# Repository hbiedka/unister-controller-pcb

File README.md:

## Dude, I need professional-looking PCB with <n> dry-contact relays, <m> 230V on/off relays, <x> inputs and <y> opto-isolated inputs

After ~10 similar projects I used to make using perfboards and PCBs etched at home I have created this PCB project to utillize it in as many automation projects as possible.

|  |  |
|---|---|
| Front | Back |

# What does it have

* 2.54 mm perfboard-like field for whatever you want
* 4 relays
  * NO/NC dry contact
  * fused AC output with N and PE split into 2 circuits protected by separated fuses 
* 8x terminal outputs for general purpose (6 of them can be easily connected to GND
* 2x optoinolated input
  * dry contact
  * low-voltage wet contact
  * AC wet contact
* AC to low voltage converted (12V, 5V or similar) using HiLink HLK series
* optional LDO or DC/DC converter (the net is called 5V but it can be any voltage by using proper LDO or converter)
* power LED diode

# Some projects I have done based on this PCB

| | |
|---|---|
|  |  |

# Configuration and customisation options

## Relays

| Footprint | Dry contact output | Wet contact output (AC voltage out) |
|---|---|---|
| Kn_DRY (closer to relay) | Populate | Do not populate |
| Kn_230VAC (closer to edge) | Do not populate | Populate |
| KN_WET jumper | Do not populate | Populate using ~1mm^2 wire |

If you are using wet contact output(s), remember to populate F2 or F3 by fuse holder and provide a proper fuse. **Remember to select proper amperage based on fuse rate and wiring**

### Negative voltage controlled coils with common VCC voltage (recommended)
If you would like to use eg. NPN or MOSFET-N transistor to drive relay coils and supply it from Hi-Link supply voltage output:
* Short COM_RELAY with VCC - the best way is to use solder nieghbor points near D4
* Solder suppression diodes according to PCB symbol (bar is cathode)

### Negative voltage controlled coils with common LDO/converter output voltage
Like above, but short COM_RELAY to 5V net

### Positive voltage controlled coils with common ground
If you would like to use PNP or MOSFET-P transistors to drive relay coils:
* Short COM_RELAY with GND
* Solder suppression diodes **opposite to PCB symbol** (bar is anode)

## Optoisolated inputs

| Footprint | Dry contact (positive) | Dry contact (negative) | Wet contact (low voltage) | Wet contact (AC voltage) |
|---|---|---|---|---|
| J10/J11 | Solder 2-pole terminal to pins 1-2 (left), short pins 3-4 | Solder 2-pole terminal to pins 3-4 (right), short pins 1-2 | Solder 2-pole terminal to pins 2-3 (middle) | Solder 2-pole terminal to pins 2-3 (middle) |
| D6/D8 | Short | Short | Short | Populate |
| R3/R4 | Short | Short | Short | Populate |
| C4/C6 | Do not populate | Do not populate | Do not populate | Populate |
| D7/D9 | Do not populate | Do not populate | Do not populate | Populate |

For all cases:
* Populate R2/R5 - use proper resistance to provide suitable diode current with nominal voltage
* Use PC817 or similar transoptor

## Single DC voltage (no DC/DC or LDO)

Short pins 1 and 3 of U1

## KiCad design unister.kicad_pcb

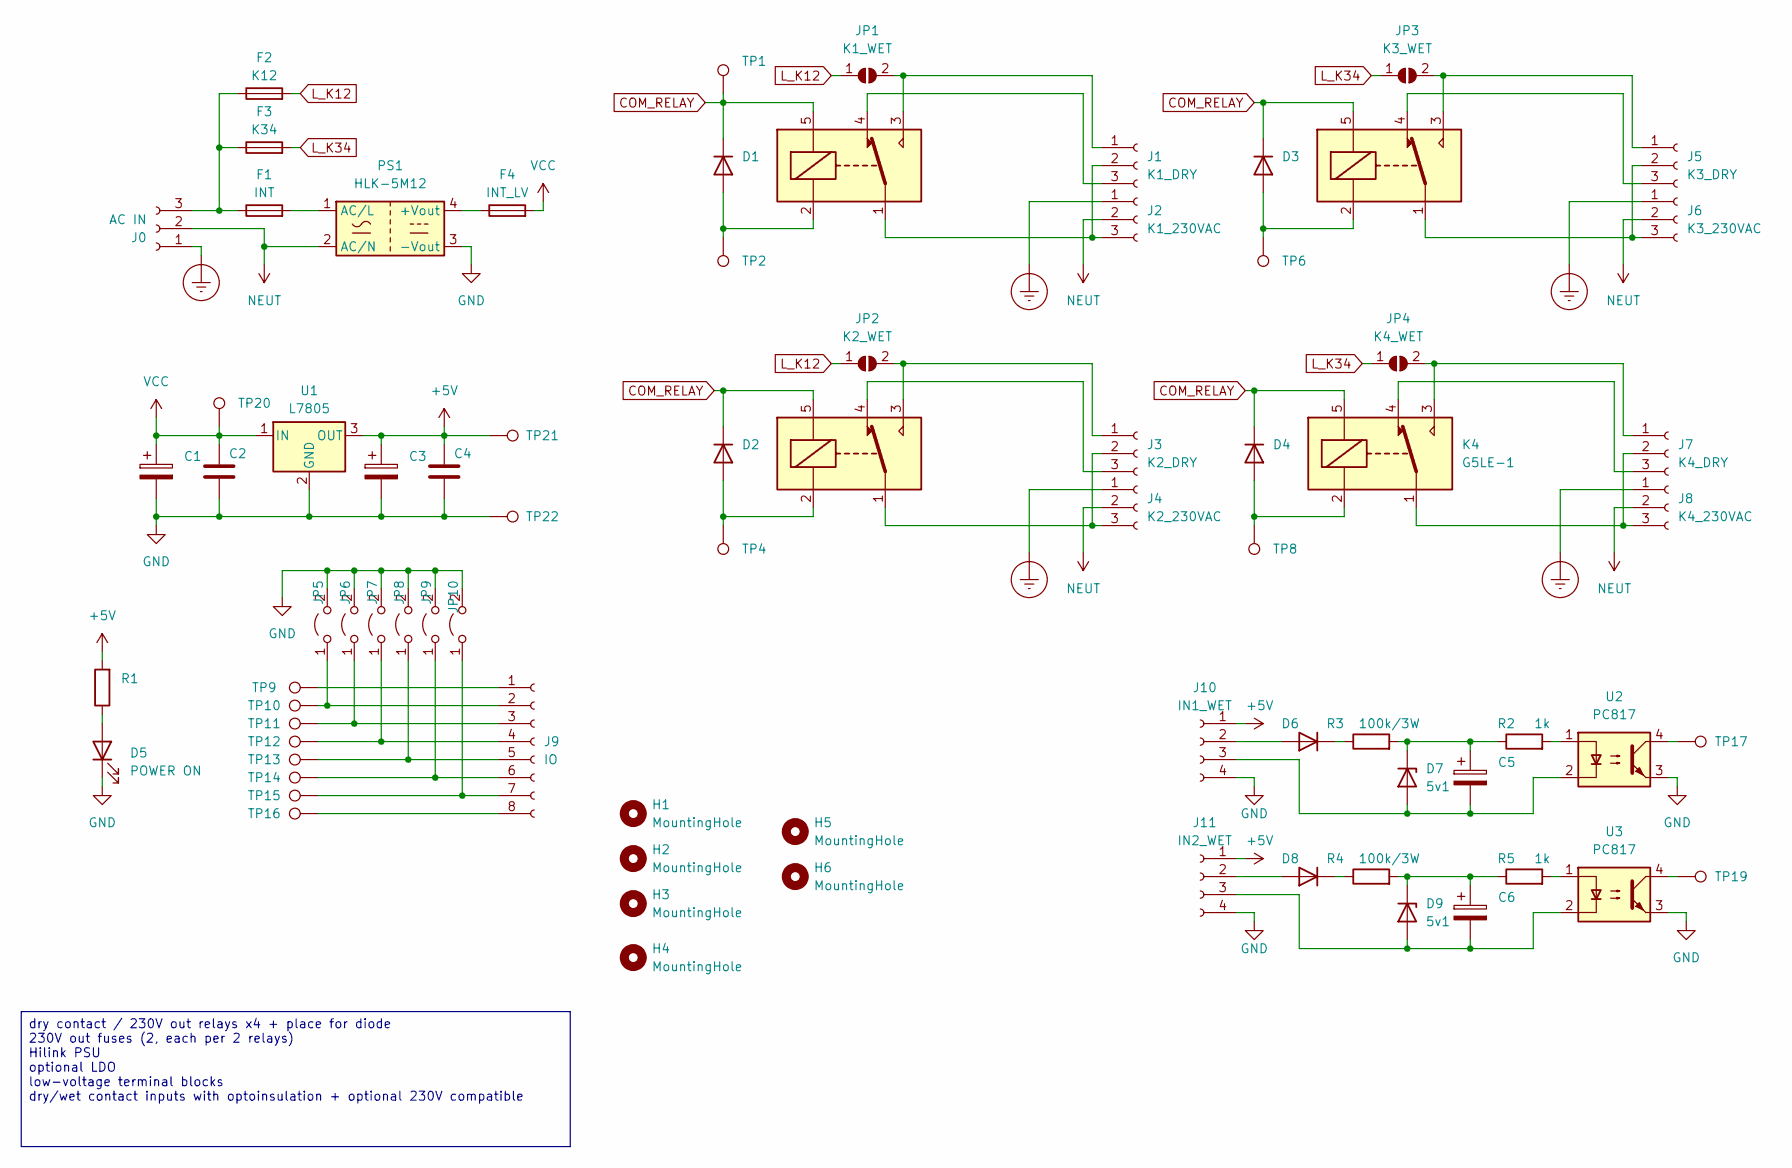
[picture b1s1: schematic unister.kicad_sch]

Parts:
C1, C3, C5, C6: C_Polarized; C_Radial_D10.0mm_H20.0mm_P5.00mm
C2, C4: C; C_Rect_L7.0mm_W3.5mm_P2.50mm_P5.00mm
D1, D2, D3, D4: 1N4007; D_DO-41_SOD81_P10.16mm_Horizontal
D5: POWER ON; LED_D3.0mm
D6, D8: D; D_DO-41_SOD81_P10.16mm_Horizontal
D7, D9: 5v1; D_DO-15_P5.08mm_Vertical_AnodeUp
F1: INT; Fuse_BelFuse_0ZRE0005FF_L8.3mm_W3.8mm
F2: K12; Fuseholder_Clip-5x20mm_Keystone_3512_Inline_P23.62x7.27mm_D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
F3: K34; Fuseholder_Clip-5x20mm_Keystone_3512_Inline_P23.62x7.27mm_D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
F4: INT_LV; Fuse_BelFuse_0ZRE0005FF_L8.3mm_W3.8mm
H1, H2, H3, H4, H5, H6: MountingHole; MountingHole_2.2mm_M2
J0: AC IN; PhoenixContact_MCV_1,5_3-G-5.08_1x03_P5.08mm_Vertical
J1: K1_DRY; PhoenixContact_MCV_1,5_3-G-5.08_1x03_P5.08mm_Vertical
J2: K1_230VAC; PhoenixContact_MCV_1,5_3-G-5.08_1x03_P5.08mm_Vertical
J3: K2_DRY; PhoenixContact_MCV_1,5_3-G-5.08_1x03_P5.08mm_Vertical
J4: K2_230VAC; PhoenixContact_MCV_1,5_3-G-5.08_1x03_P5.08mm_Vertical
J5: K3_DRY; PhoenixContact_MCV_1,5_3-G-5.08_1x03_P5.08mm_Vertical
J6: K3_230VAC; PhoenixContact_MCV_1,5_3-G-5.08_1x03_P5.08mm_Vertical
J7: K4_DRY; PhoenixContact_MCV_1,5_3-G-5.08_1x03_P5.08mm_Vertical
J8: K4_230VAC; PhoenixContact_MCV_1,5_3-G-5.08_1x03_P5.08mm_Vertical
J9: IO; PhoenixContact_MCV_1,5_8-G-5.08_1x08_P5.08mm_Vertical
J10: IN1_WET; PhoenixContact_MCV_1,5_4-G-5.08_1x04_P5.08mm_Vertical
J11: IN2_WET; PhoenixContact_MCV_1,5_4-G-5.08_1x04_P5.08mm_Vertical
JP1: K1_WET; TestPoint_2Pads_Pitch5.08mm_Drill1.3mm
JP2: K2_WET; TestPoint_2Pads_Pitch5.08mm_Drill1.3mm
JP3: K3_WET; TestPoint_2Pads_Pitch5.08mm_Drill1.3mm
JP4: K4_WET; TestPoint_2Pads_Pitch5.08mm_Drill1.3mm
JP5, JP6, JP7, JP8, JP9, JP10: SolderJumper-2_P1.3mm_Open_RoundedPad1.0x1.5mm
K1, K2, K3, K4: G5LE-1; Relay_SPDT_Omron-G5LE-1
PS1: HLK-5M12; Converter_ACDC_HiLink_HLK-5Mxx
R1: R; R_1206_3216Metric_Pad1.30x1.75mm_HandSolder
R2, R5: 1k; R_1206_3216Metric_Pad1.30x1.75mm_HandSolder
R3, R4: 100k/3W; R_Axial_DIN0309_L9.0mm_D3.2mm_P15.24mm_Horizontal
TP1, TP2, TP4, TP6, TP8, TP9, TP10, TP11, TP12, TP13, TP14, TP15, TP16, TP17, TP19, TP20, TP21, TP22: TestPoint; Pin_D0.7mm_L6.5mm_W1.8mm_FlatFork
U1: L7805; TO-92L_Inline_Wide
U2, U3: PC817; DIP-4_W7.62mm

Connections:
+5V: C3.1, C4.1, J10.1, J11.1, R1.2, TP21.1, U1.3 (OUT)
COM_RELAY: D1.1 (K), D2.1 (K), D3.1 (K), D4.1 (K), K1.5, K2.5, K3.5, K4.5, TP1.1
Earth_Protective: J0.1, J2.1, J4.1, J6.1, J8.1
GND: C1.2, C2.2, C3.2, C4.2, D5.1 (K), J10.4, J11.4, JP5.2 (B), JP6.2 (B), JP7.2 (B), JP8.2 (B), JP9.2 (B), JP10.2 (B), PS1.3 (-Vout), TP22.1, U1.2 (GND), U2.3, U3.3
L_K12: F2.2, JP1.1 (A), JP2.1 (A)
L_K34: F3.2, JP3.1 (A), JP4.1 (A)
NEUT: J0.2, J2.2, J4.2, J6.2, J8.2, PS1.2 (AC/N)
unnamed: D1.2 (A), K1.2, TP2.1
unnamed: D2.2 (A), K2.2, TP4.1
unnamed: D3.2 (A), K3.2, TP6.1
unnamed: D4.2 (A), K4.2, TP8.1
unnamed: D5.2 (A), R1.1
unnamed: D6.2 (A), J10.2
unnamed: D6.1 (K), R3.1
unnamed: C5.2, D7.2 (A), J10.3, U2.2
unnamed: C5.1, D7.1 (K), R2.1, R3.2
unnamed: D8.2 (A), J11.2
unnamed: D8.1 (K), R4.1
unnamed: C6.2, D9.2 (A), J11.3, U3.2
unnamed: C6.1, D9.1 (K), R4.2, R5.1
unnamed: F1.1, F2.1, F3.1, J0.3
unnamed: J1.1, JP1.2 (B), K1.3
unnamed: J1.2, J2.3, K1.1
unnamed: J1.3, K1.4
unnamed: J3.1, JP2.2 (B), K2.3
unnamed: J3.2, J4.3, K2.1
unnamed: J3.3, K2.4
unnamed: J5.1, JP3.2 (B), K3.3
unnamed: J5.2, J6.3, K3.1
unnamed: J5.3, K3.4
unnamed: J7.1, JP4.2 (B), K4.3
unnamed: J7.2, J8.3, K4.1
unnamed: J7.3, K4.4
unnamed: J9.1, TP9.1
unnamed: J9.2, JP5.1 (A), TP10.1
unnamed: J9.3, JP6.1 (A), TP11.1
unnamed: J9.4, JP7.1 (A), TP12.1
unnamed: J9.5, JP8.1 (A), TP13.1
unnamed: J9.6, JP9.1 (A), TP14.1
unnamed: J9.7, JP10.1 (A), TP15.1
unnamed: J9.8, TP16.1
unnamed: F4.1, PS1.4 (+Vout)
unnamed: F1.2, PS1.1 (AC/L)
unnamed: R2.2, U2.1
unnamed: R5.2, U3.1
unnamed: TP17.1, U2.4
unnamed: TP19.1, U3.4
VCC: C1.1, C2.1, F4.2, TP20.1, U1.1 (IN)

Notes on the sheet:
dry contact / 230V out relays x4 + place for diode 230V out fuses (2, each per 2 relays) Hilink PSU optional LDO low-voltage terminal blocks dry/wet contact inputs with optoinsulation + optional 230V compatible

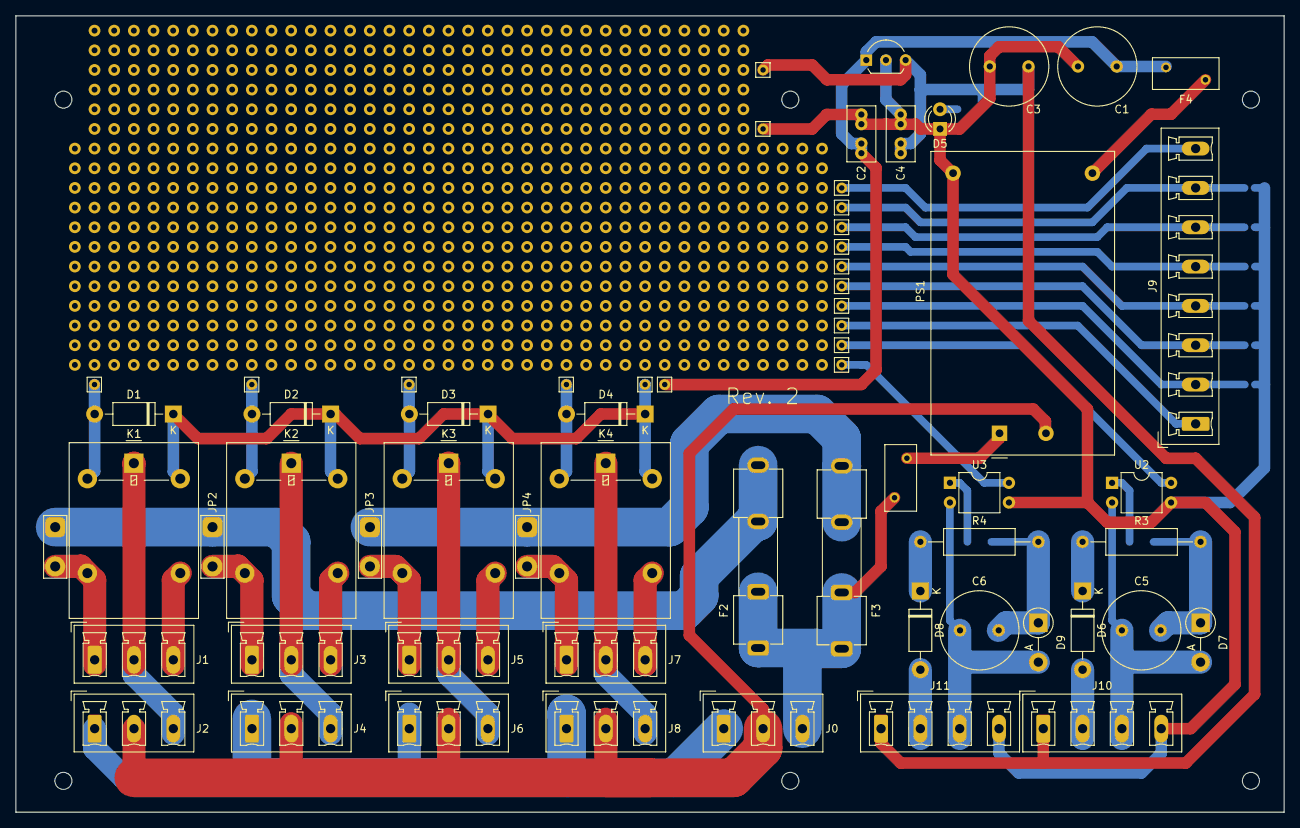
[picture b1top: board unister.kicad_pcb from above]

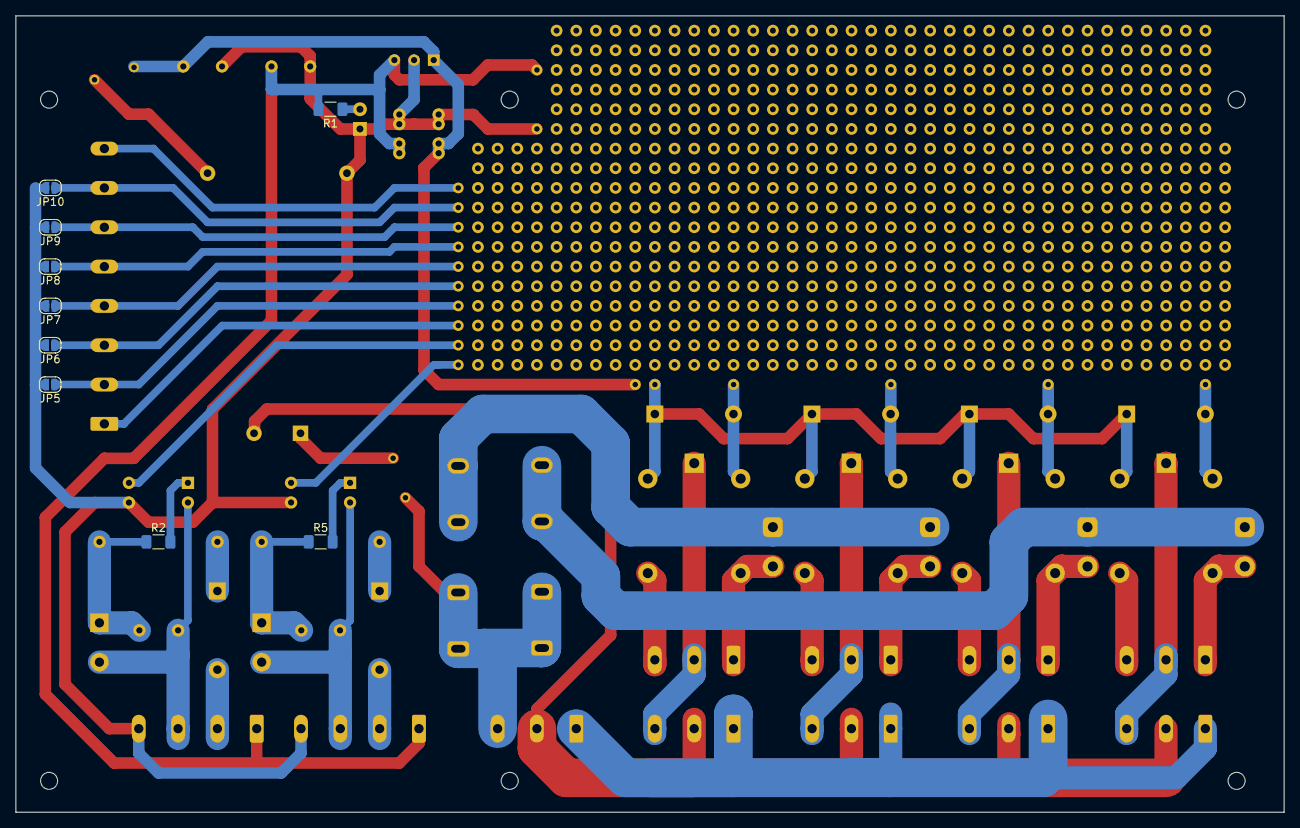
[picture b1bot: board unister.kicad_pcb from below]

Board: 2 copper layers, 163.8 x 102.9 mm, 78 parts (9 on the bottom side), 48 nets.

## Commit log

2025-07-27 Version 1: add production files
2025-08-12 Revision 2: Grow fuses distance, move mounting holes
2025-08-12 README.md: changed part of configuration descriptions to tables
2025-08-24 Revision 2: Add print, export production files
2025-08-24 Added photos
